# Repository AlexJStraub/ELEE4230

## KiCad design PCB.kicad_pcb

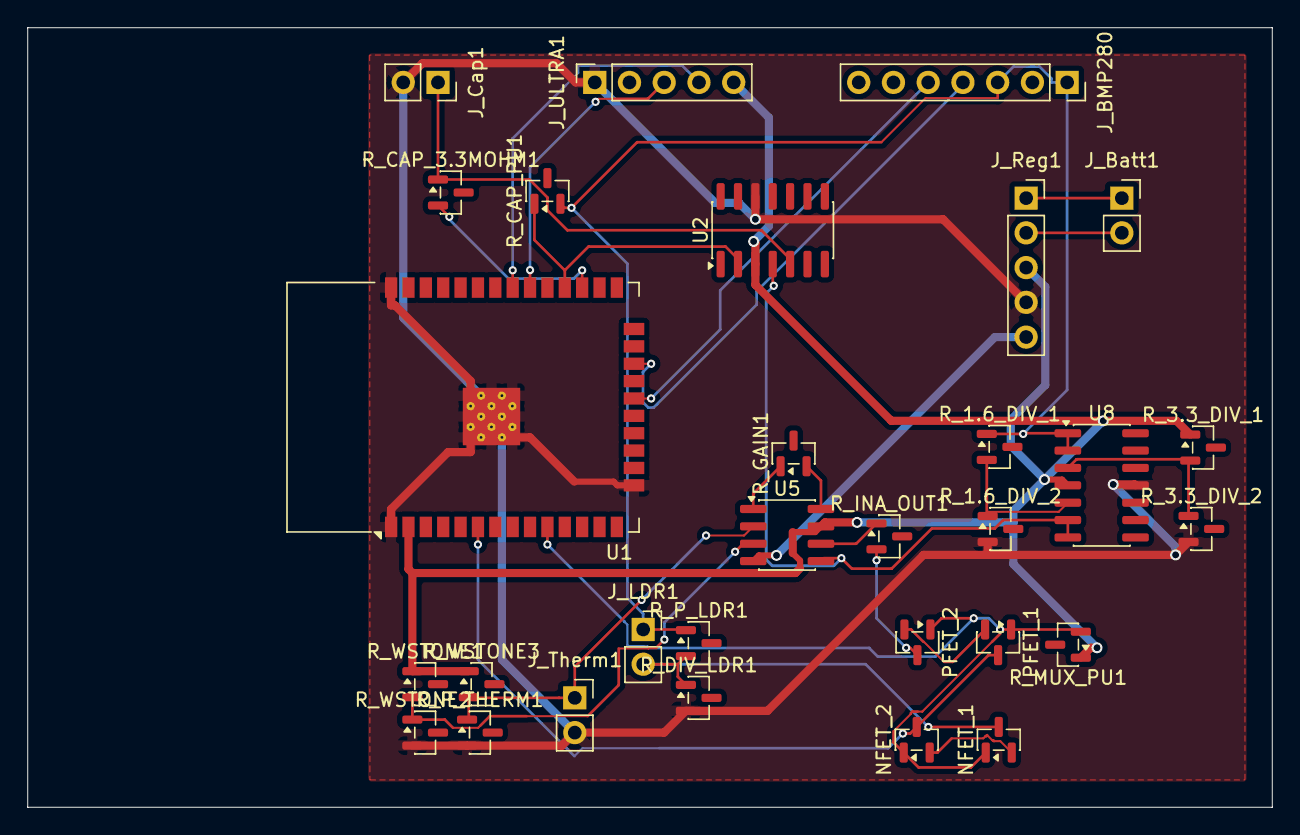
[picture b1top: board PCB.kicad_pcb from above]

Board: 2 copper layers, 91.0 x 57.0 mm, 30 parts (0 on the bottom side), 27 nets.

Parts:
J_BMP280: Conn_01x07_Socket; PinSocket_1x07_P2.54mm_Vertical
J_Batt1: Conn_01x02_Socket; PinSocket_1x02_P2.54mm_Vertical
J_Cap1: Conn_01x02_Socket; PinSocket_1x02_P2.54mm_Vertical
J_LDR1: Conn_01x02_Socket; PinSocket_1x02_P2.54mm_Vertical
J_Reg1: DD1718PA; PinSocket_1x05_P2.54mm_Vertical
J_Therm1: Conn_01x02_Socket; PinSocket_1x02_P2.54mm_Vertical
J_ULTRA1: Conn_01x05_Socket; PinSocket_1x05_P2.54mm_Vertical
NFET_1, NFET_2: AO3400A; SOT-23
PFET_1, PFET_2: AO3401A; SOT-23
R_1.6_DIV_1, R_1.6_DIV_2, R_3.3_DIV_1: 10000; SOT-23
R_3.3_DIV_2: 20000; SOT-23
R_CAP_3.3MOHM1: 3300000; SOT-23
R_CAP_PU1: 10000; SOT-23
R_DIV_LDR1: 10000; SOT-23
R_GAIN1: 20000; SOT-23
R_INA_OUT1: 10000; SOT-23
R_MUX_PU1: 10000; SOT-23
R_P_LDR1: 7000; SOT-23
R_P_THERM1: 700; SOT-23
R_WSTONE1, R_WSTONE2, R_WSTONE3: 400; SOT-23
U1: ESP32-WROOM-32
U2: LM339; SOIC-14_3.9x8.7mm_P1.27mm
U5: INA129; SOIC-8_3.9x4.9mm_P1.27mm
U8: TL084; SOIC-14_3.9x8.7mm_P1.27mm

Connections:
+5V: J_Reg1.3, J_ULTRA1.5, R_3.3_DIV_1.1, R_MUX_PU1.1, R_WSTONE1.1, R_WSTONE3.1, U1.2 (VDD), U2.3 (V+), U5.7 (V+), U8.4 (V+)
-5V: J_Reg1.5, U5.4 (V-)
GND: J_Cap1.2, J_Reg1.4, J_Therm1.2, J_ULTRA1.1, R_1.6_DIV_2.2, R_3.3_DIV_2.2, R_DIV_LDR1.2, R_P_THERM1.2, R_WSTONE2.2, U1.1 (GND), U1.15 (GND), U1.38 (GND), U1.39 (GND), U2.12 (V-), U8.11 (V-)
unnamed: J_BMP280.1, J_BMP280.3, J_LDR1.1, R_1.6_DIV_1.1, R_CAP_PU1.2, R_P_LDR1.1, U8.1, U8.2 (-)
unnamed: J_BMP280.4, U1.22 (SDI/SD1)
unnamed: J_BMP280.5, U1.20 (SCK/CLK)
unnamed: J_Batt1.1, J_Reg1.1
unnamed: J_Batt1.2, J_Reg1.2
unnamed: J_Cap1.1, R_CAP_3.3MOHM1.1, U2.5 (+)
unnamed: J_LDR1.2, NFET_1.3 (D), R_DIV_LDR1.1, R_P_LDR1.2
unnamed: J_Therm1.1, R_P_THERM1.1, R_WSTONE3.2, U5.2 (-)
unnamed: J_ULTRA1.3, U1.30 (IO18)
unnamed: J_ULTRA1.4, U1.31 (IO19)
unnamed: NFET_1.1 (G), NFET_2.1 (G), PFET_1.1 (G), PFET_2.1 (G), R_MUX_PU1.2, U1.10 (IO25)
unnamed: NFET_1.2 (S), NFET_2.2 (S)
unnamed: NFET_2.3 (D), PFET_1.3 (D), U1.6 (IO34)
unnamed: PFET_1.2 (S), PFET_2.2 (S)
unnamed: PFET_2.3 (D), R_INA_OUT1.2
unnamed: R_GAIN1.1, U5.1 (Rg)
unnamed: R_GAIN1.2, U5.8 (Rg)
unnamed: R_INA_OUT1.1, U5.6
unnamed: R_CAP_3.3MOHM1.2, U1.27 (IO16)
unnamed: R_CAP_PU1.1, U1.28 (IO17), U2.2
unnamed: U2.4 (-), U5.5 (Ref), U8.6 (-), U8.7
unnamed: R_WSTONE1.2, R_WSTONE2.1, U5.3 (+)
unnamed: R_3.3_DIV_1.2, R_3.3_DIV_2.1, U8.3 (+)
unnamed: R_1.6_DIV_1.2, R_1.6_DIV_2.1, U8.5 (+)
